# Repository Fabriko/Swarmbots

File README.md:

# Swarmbots

[Attribution-ShareAlike 4.0 International](http://creativecommons.org/licenses/by-sa/4.0/)

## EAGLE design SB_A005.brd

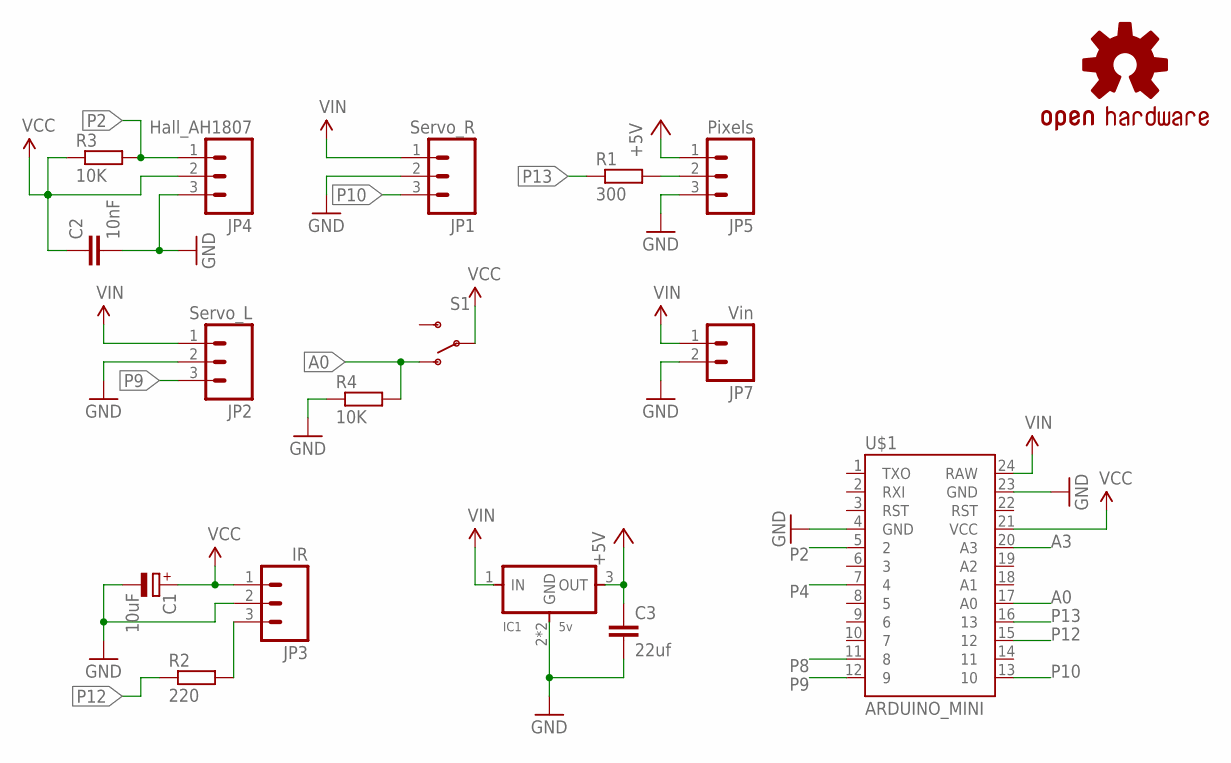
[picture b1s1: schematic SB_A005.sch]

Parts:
C1: 10uF; C/6032-28R
C2: 10nF; C1206
C3: 22uf; C1206K
IC1: 5v; SOT223
JP1: Servo_R; 1X03_LONGPADS
JP2: Servo_L; 1X03_LONGPADS
JP3: IR; 1X03_NO_SILK
JP4: Hall_AH1807; 1X03_NO_SILK
JP5: Pixels; 1X03_LONGPADS
JP7: Vin; 1X02_LONGPADS
LOGO1: OSHW-LOGOS; OSHW-LOGO-S
R1: 300; M1206
R2: 220; M1206
R3, R4: 10K; M1206
S1: SWITCH-SPDTSMD2; SWITCH-SPDT-SMD
U$1: ARDUINO_MINI

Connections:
+5V: C3.1, IC1.3 (OUT), JP5.1
A0: R4.2, S1.1 (O), U$1.17 (A0)
A3: U$1.20 (A3)
GND: C1.-, C2.2, C3.2, IC1.2 (GND), IC1.4 (GND), JP1.2, JP2.2, JP3.2, JP4.3, JP5.3, JP7.2, R4.1, U$1.4 (GND), U$1.23 (GND)
unnamed: JP3.3, R2.2
unnamed: JP5.2, R1.2
P2: JP4.1, R3.2, U$1.5 (2)
P4: U$1.7 (4)
P8: U$1.11 (8)
P9: JP2.3, U$1.12 (9)
P10: JP1.3, U$1.13 (10)
P12: R2.1, U$1.15 (12)
P13: R1.1, U$1.16 (13)
VCC: C1.+, C2.1, JP3.1, JP4.2, R3.1, S1.2, U$1.21 (VCC)
VIN: IC1.1 (IN), JP1.1, JP2.1, JP7.1, U$1.24 (RAW)

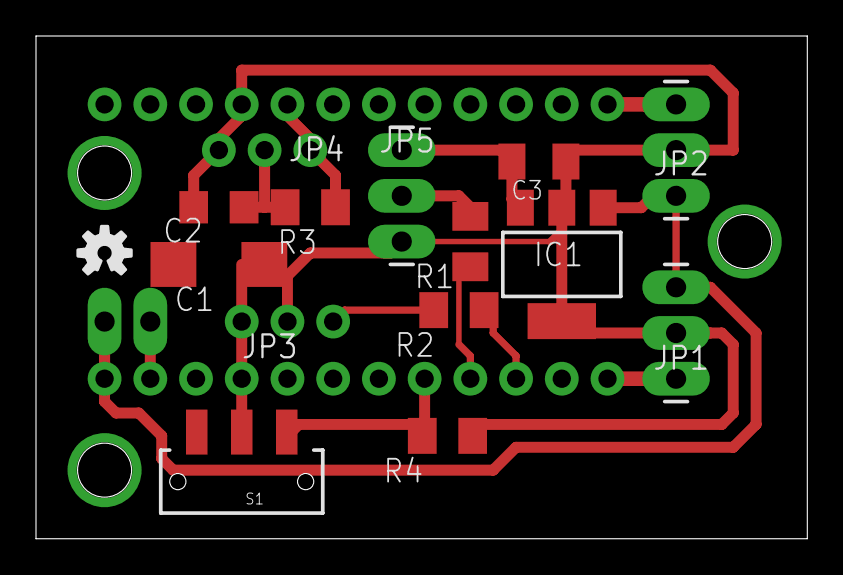
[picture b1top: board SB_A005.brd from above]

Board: 2 copper layers, 42.9 x 27.9 mm, 17 parts (1 on the bottom side), 12 nets.

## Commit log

2015-12-01 inital setup
2015-12-01 prototype schematic
2015-12-01 added BOM

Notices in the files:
SB_A005.sch:
This work is licensed under
Creative Commons Attribution-ShareAlike 4.0
parts and their libraries:
SparkFun-Connectors: Licensing: Creative Commons ShareAlike 4.0 International - https://creativecommons.org/licenses/by-sa/4.0
